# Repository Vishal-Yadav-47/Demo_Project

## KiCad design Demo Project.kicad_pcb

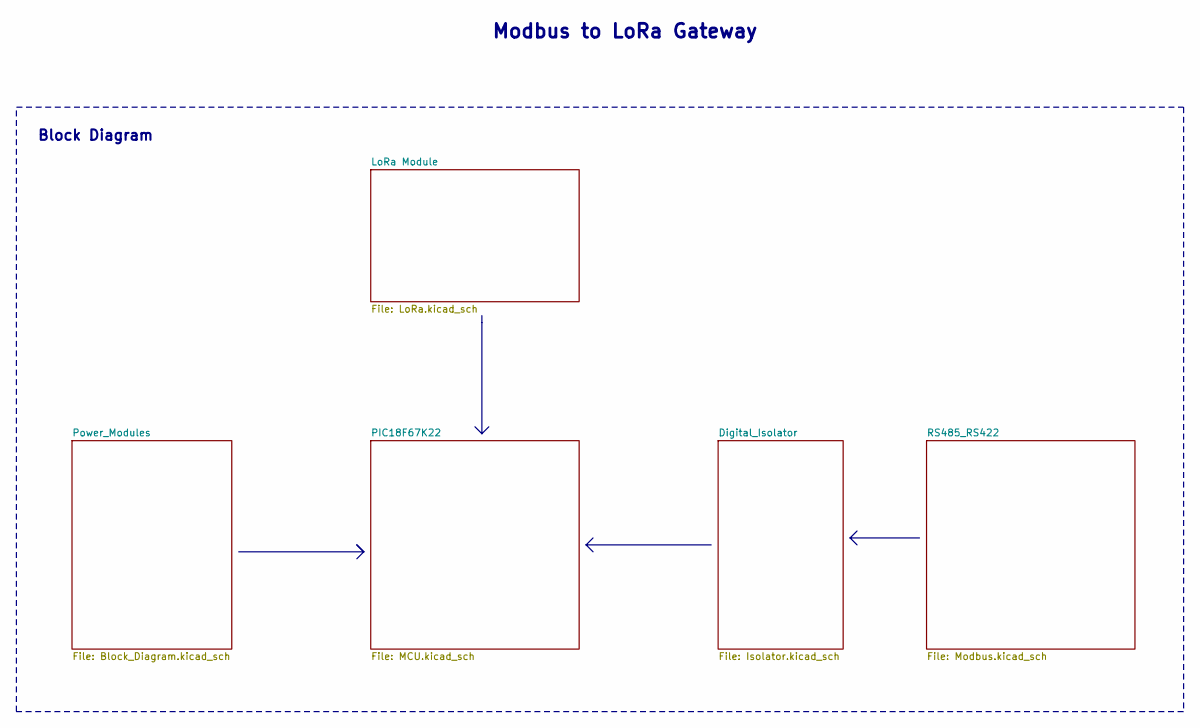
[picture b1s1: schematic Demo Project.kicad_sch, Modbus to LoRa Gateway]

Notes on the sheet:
Modbus to LoRa Gateway
Block Diagram

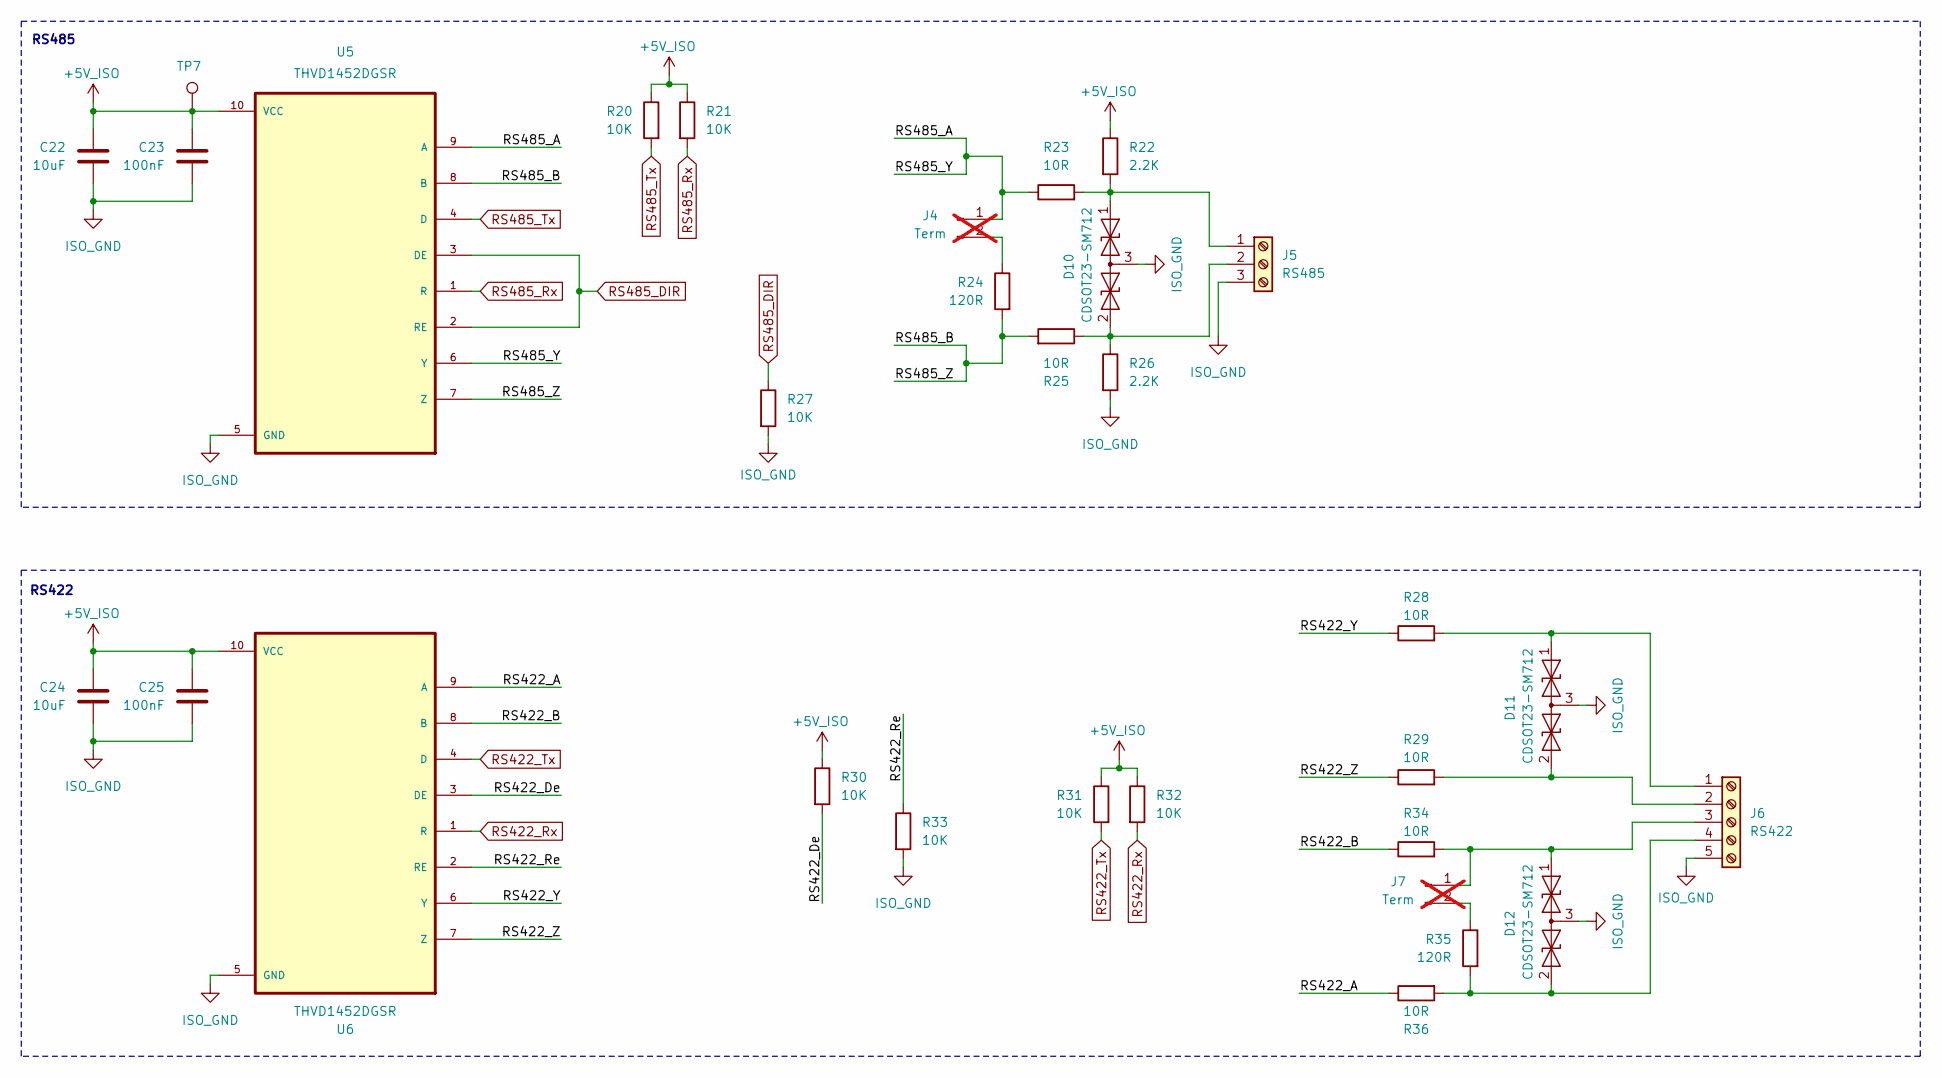
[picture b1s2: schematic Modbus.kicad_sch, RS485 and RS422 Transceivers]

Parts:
C22, C24: 10uF; C_0805_2012Metric
C23, C25: 100nF; C_0805_2012Metric
D10, D11, D12: CDSOT23-SM712; SOT-23
J4, J7: Term; PinHeader_1x02_P2.54mm_Vertical; not fitted
J5: RS485; TerminalBlock_CUI_TB007-508-03_1x03_P5.08mm_Horizontal
J6: RS422; TerminalBlock_CUI_TB007-508-05_1x05_P5.08mm_Horizontal
R20, R21, R27, R30, R31, R32, R33: 10K; R_0805_2012Metric
R22, R26: 2.2K; R_0805_2012Metric
R23, R25, R28, R29, R34, R36: 10R; R_0805_2012Metric
R24, R35: 120R; R_1206_3216Metric
TP7: TestPoint; TestPoint_Pad_D1.0mm
U5, U6: THVD1452DGSR; SOP50P490X110-10N

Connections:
+5V_ISO: C22.1, C23.1, C24.1, C25.1, R20.1, R21.1, R22.1, R30.1, R31.1, R32.1, TP7.1 (1_1), U5.10 (VCC), U6.10 (VCC); also elsewhere on the board
/RS485_RS422/RS422_A: R36.1, U6.9 (A)
/RS485_RS422/RS422_B: R34.1, U6.8 (B)
/RS485_RS422/RS422_De: R30.2, U6.3 (DE)
/RS485_RS422/RS422_Re: R33.1, U6.2 (RE)
/RS485_RS422/RS422_Y: R28.1, U6.6 (Y)
/RS485_RS422/RS422_Z: R29.1, U6.7 (Z)
/RS485_RS422/RS485_A: J4.1, R23.1, U5.6 (Y), U5.9 (A)
/RS485_RS422/RS485_B: R24.2, R25.2, U5.7 (Z), U5.8 (B)
ISO_GND: C22.2, C23.2, C24.2, C25.2, D10.3 (common), D11.3 (common), D12.3 (common), J5.3, J6.5, R26.2, R27.2, R33.2, U5.5 (GND), U6.5 (GND); also elsewhere on the board
unnamed: D10.1 (A1), J5.1, R22.2, R23.2
unnamed: D10.2 (A2), J5.2, R25.1, R26.1
unnamed: D11.1 (A1), J6.1, R28.2
unnamed: D11.2 (A2), J6.2, R29.2
unnamed: D12.1 (A1), J6.3, J7.1, R34.2
unnamed: D12.2 (A2), J6.4, R35.2, R36.2
unnamed: J4.2, R24.1
unnamed: J7.2, R35.1
RS422_Rx: R32.2, U6.1 (R); also elsewhere on the board
RS422_Tx: R31.2, U6.4 (D); also elsewhere on the board
RS485_DIR: R27.1, U5.2 (RE), U5.3 (DE); also elsewhere on the board
RS485_Rx: R21.2, U5.1 (R); also elsewhere on the board
RS485_Tx: R20.2, U5.4 (D); also elsewhere on the board

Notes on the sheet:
RS422
RS485

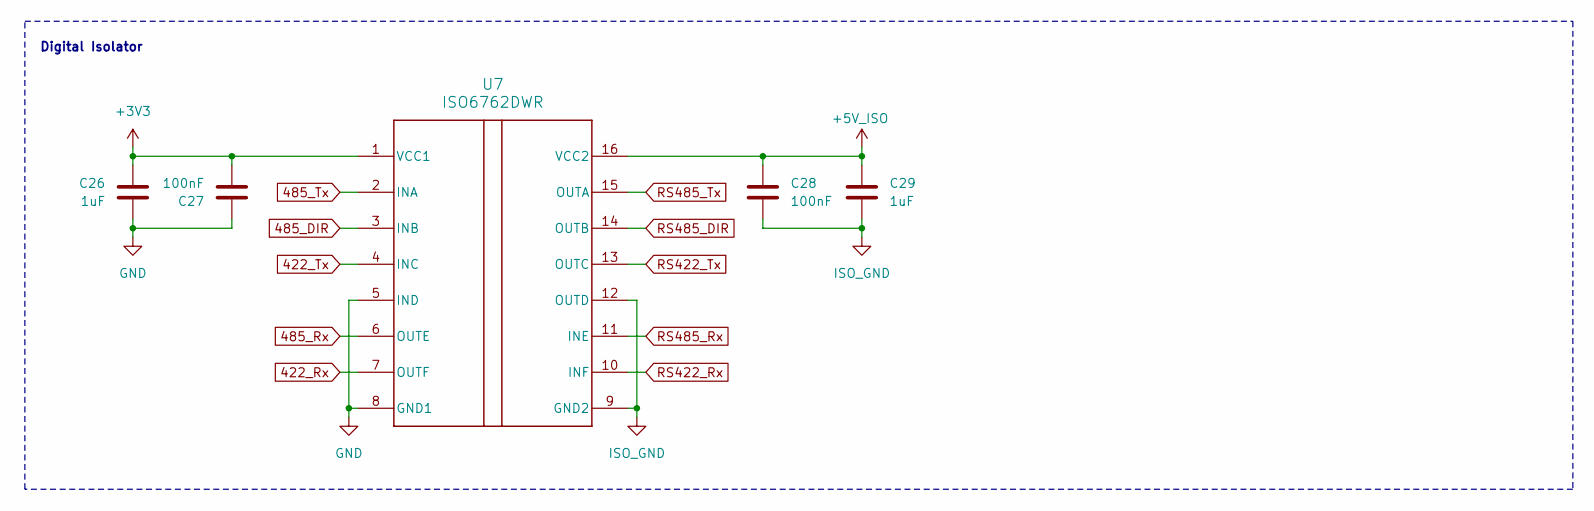
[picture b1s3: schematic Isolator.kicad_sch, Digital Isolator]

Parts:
C26, C29: 1uF; C_0805_2012Metric
C27, C28: 100nF; C_0805_2012Metric
U7: ISO6762DWR; SOIC-16W_7.5x12.8mm_P1.27mm

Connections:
422_Rx: U7.7 (OUTF); also elsewhere on the board
422_Tx: U7.4 (INC); also elsewhere on the board
485_DIR: U7.3 (INB); also elsewhere on the board
485_Rx: U7.6 (OUTE); also elsewhere on the board
485_Tx: U7.2 (INA); also elsewhere on the board
+3V3: C26.2, C27.2, U7.1 (VCC1); also elsewhere on the board
+5V_ISO: C28.1, C29.1, U7.16 (VCC2); also elsewhere on the board
GND: C26.1, C27.1, U7.5 (IND), U7.8 (GND1); also elsewhere on the board
ISO_GND: C28.2, C29.2, U7.9 (GND2), U7.12 (OUTD); also elsewhere on the board
RS422_Rx: U7.10 (INF); also elsewhere on the board
RS422_Tx: U7.13 (OUTC); also elsewhere on the board
RS485_DIR: U7.14 (OUTB); also elsewhere on the board
RS485_Rx: U7.11 (INE); also elsewhere on the board
RS485_Tx: U7.15 (OUTA); also elsewhere on the board

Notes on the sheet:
Digital Isolator

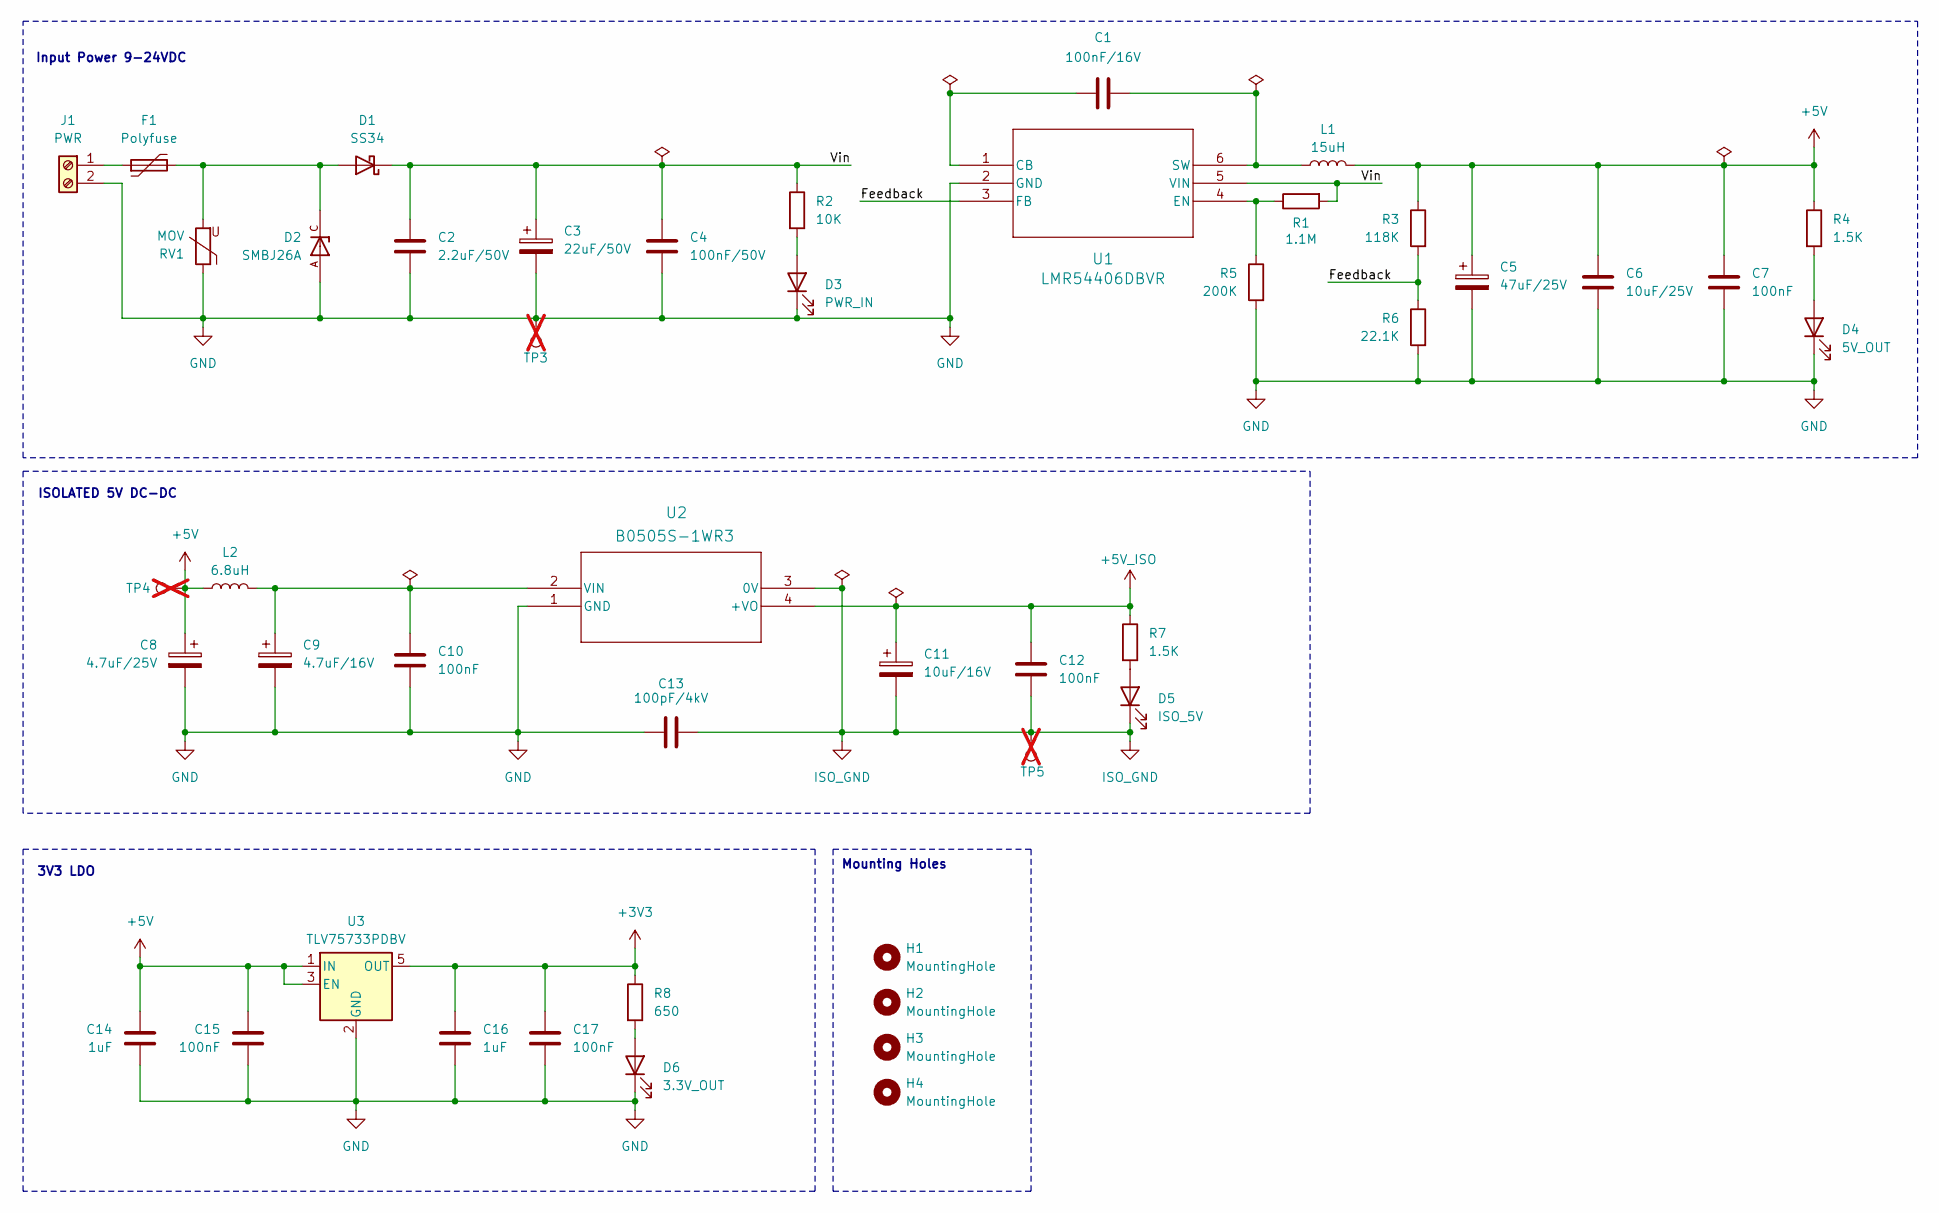
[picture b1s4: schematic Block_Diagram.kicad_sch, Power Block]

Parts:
C1: 100nF/16V; C_0805_2012Metric
C2: 2.2uF/50V; C_0805_2012Metric
C3: 22uF/50V; CP_Elec_8x10.5
C4: 100nF/50V; C_0805_2012Metric
C5: 47uF/25V; CP_Elec_6.3x5.4
C6: 10uF/25V; C_0805_2012Metric
C7, C10, C12, C15, C17: 100nF; C_0805_2012Metric
C8: 4.7uF/25V; CP_Elec_4x5.4
C9: 4.7uF/16V; CP_Elec_4x5.4
C11: 10uF/16V; CP_Elec_5x5.4
C13: 100pF/4kV; C_1812_4532Metric
C14, C16: 1uF; C_0805_2012Metric
D1: SS34; D_SMA
D2: SMBJ26A; DIOM4336X265N; PARTREV F2102
D3: PWR_IN; LED_0805_2012Metric
D4: 5V_OUT; LED_0805_2012Metric
D5: ISO_5V; LED_0805_2012Metric
D6: 3.3V_OUT; LED_0805_2012Metric
F1: Polyfuse; Fuse_2920_7451Metric
H1, H2, H3, H4: MountingHole; MountingHole_3.2mm_M3_DIN965_Pad_TopBottom
J1: PWR; TerminalBlock_CUI_TB007-508-02_1x02_P5.08mm_Horizontal
L1: 15uH; L_Coilcraft_XAL5050-XXX
L2: 6.8uH; L_Wuerth_MAPI-4020
R1: 1.1M; R_0805_2012Metric
R2: 10K; R_0805_2012Metric
R3: 118K; R_0805_2012Metric
R4, R7: 1.5K; R_0805_2012Metric
R5: 200K; R_0805_2012Metric
R6: 22.1K; R_0805_2012Metric
R8: 650; R_0805_2012Metric
RV1: MOV; RV_Disc_D7mm_W3.7mm_P5mm
TP3, TP4, TP5: TestPoint; TestPoint_Pad_D1.0mm; not fitted
U1: LMR54406DBVR; SOT-23-6
U2: B0505S-1WR3; Converter_DCDC_RECOM_R-78S-0.1_THT
U3: TLV75733PDBV; SOT-23-5

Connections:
+3V3: C16.1, C17.1, R8.1, U3.5 (OUT); also elsewhere on the board
+5V: C5.1, C6.1, C7.1, C8.1, C14.1, C15.1, L1.2, L2.1, R3.1, R4.1, TP4.1 (1_1), U3.1 (IN), U3.3 (EN)
+5V_ISO: C11.1, C12.1, R7.1, U2.4 (+VO); also elsewhere on the board
/Power_Modules/Feedback: R3.2, R6.1, U1.3 (FB)
/Power_Modules/Vin: C2.1, C3.1, C4.1, D1.1 (K), R1.2, R2.1, U1.5 (VIN)
GND: C2.2, C3.2, C4.2, C5.2, C6.2, C7.2, C8.2, C9.2, C10.2, C13.1, C14.2, C15.2, C16.2, C17.2, D2.A, D3.1 (K), D4.1 (K), D6.1 (K), J1.2, R5.2, R6.2, RV1.1, TP3.1 (1_1), U1.2 (GND), U2.1 (GND), U3.2 (GND); also elsewhere on the board
ISO_GND: C11.2, C12.2, C13.2, D5.1 (K), TP5.1 (1_1), U2.3 (0V); also elsewhere on the board
unnamed: D1.2 (A), D2.C, F1.2, RV1.2
unnamed: D3.2 (A), R2.2
unnamed: D4.2 (A), R4.2
unnamed: D5.2 (A), R7.2
unnamed: D6.2 (A), R8.2
unnamed: F1.1, J1.1
unnamed: C1.2, U1.1 (CB)
unnamed: R1.1, R5.1, U1.4 (EN)
unnamed: C1.1, L1.1, U1.6 (SW)
unnamed: C9.1, C10.1, L2.2, U2.2 (VIN)

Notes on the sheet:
Mounting Holes
ISOLATED 5V DC-DC
3V3 LDO
Input Power 9-24VDC

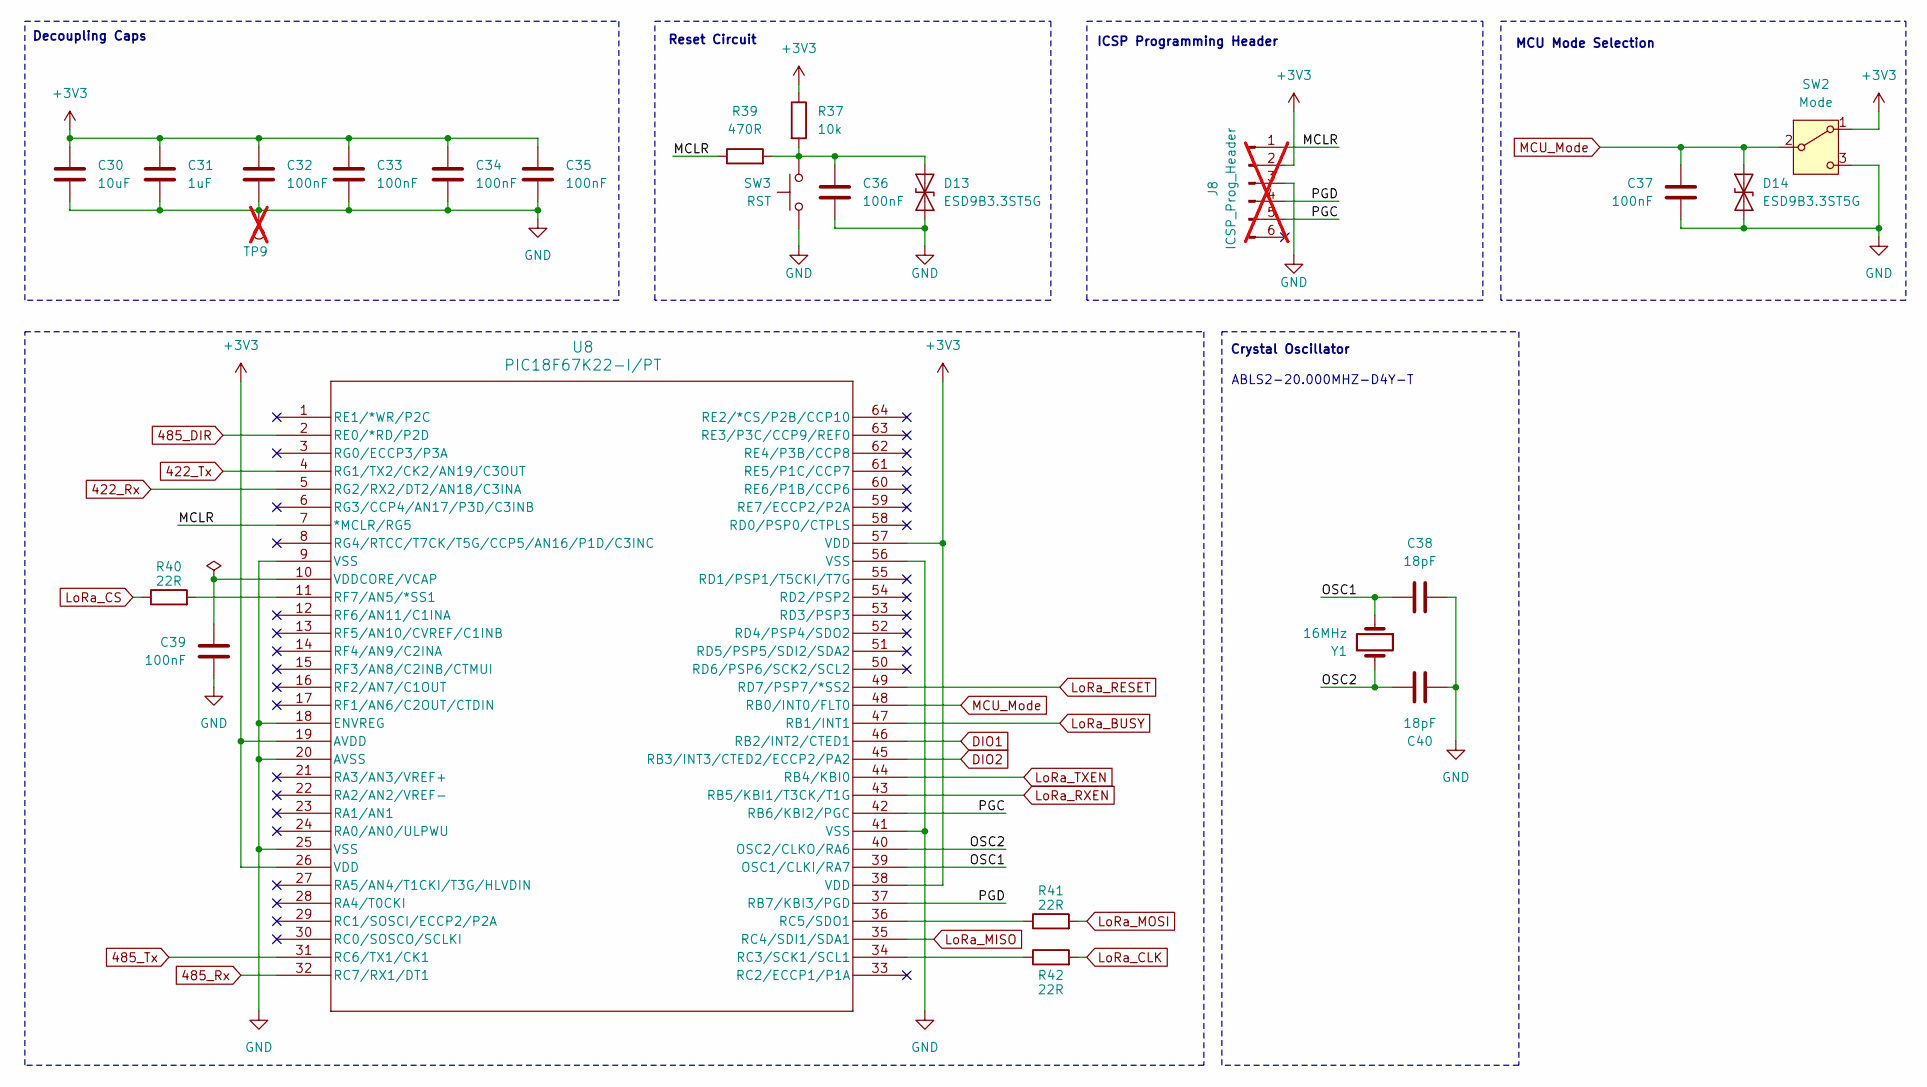
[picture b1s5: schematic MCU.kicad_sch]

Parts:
C30: 10uF; C_0805_2012Metric
C31: 1uF; C_0805_2012Metric
C32, C33, C34, C35, C36, C37, C39: 100nF; C_0805_2012Metric
C38, C40: 18pF; C_0805_2012Metric
D13, D14: ESD9B3.3ST5G; D_SOD-923
J8: ICSP_Prog_Header; PinHeader_1x06_P2.54mm_Vertical; not fitted
R37: 10k; R_0805_2012Metric
R39: 470R; R_0805_2012Metric
R40, R41, R42: 22R; R_0805_2012Metric
SW2: Mode; SW_Slide_SPDT_Straight_CK_OS102011MS2Q
SW3: RST; SW_SPST_TL3305B
TP9: TestPoint; TestPoint_Pad_D1.0mm; not fitted
U8: PIC18F67K22-I/PT; TQFP-64_10x10mm_P0.5mm
Y1: 16MHz; Crystal_SMD_HC49-SD

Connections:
422_Rx: U8.5 (RG2/RX2/DT2/AN18/C3INA); also elsewhere on the board
422_Tx: U8.4 (RG1/TX2/CK2/AN19/C3OUT); also elsewhere on the board
485_DIR: U8.2 (RE0/*RD/P2D); also elsewhere on the board
485_Rx: U8.32 (RC7/RX1/DT1); also elsewhere on the board
485_Tx: U8.31 (RC6/TX1/CK1); also elsewhere on the board
+3V3: C30.1, C31.1, C32.1, C33.1, C34.1, C35.1, J8.2, R37.1, SW2.1 (A), U8.19 (AVDD), U8.26 (VDD), U8.38 (VDD), U8.57 (VDD); also elsewhere on the board
/PIC18F67K22/MCLR: J8.1, R39.1, U8.7 (*MCLR/RG5)
/PIC18F67K22/OSC1: C38.1, U8.39 (OSC1/CLKI/RA7), Y1.1
/PIC18F67K22/OSC2: C40.2, U8.40 (OSC2/CLKO/RA6), Y1.2
/PIC18F67K22/PGC: J8.5, U8.42 (RB6/KBI2/PGC)
/PIC18F67K22/PGD: J8.4, U8.37 (RB7/KBI3/PGD)
DIO1: U8.46 (RB2/INT2/CTED1); also elsewhere on the board
DIO2: U8.45 (RB3/INT3/CTED2/ECCP2/PA2); also elsewhere on the board
GND: C30.2, C31.2, C32.2, C33.2, C34.2, C35.2, C36.2, C37.2, C38.2, C39.2, C40.1, D13.1 (A1), D14.1 (A1), J8.3, SW2.3 (C), SW3.2, TP9.1 (1_1), U8.9 (VSS), U8.18 (ENVREG), U8.20 (AVSS), U8.25 (VSS), U8.41 (VSS), U8.56 (VSS); also elsewhere on the board
LoRa_BUSY: U8.47 (RB1/INT1); also elsewhere on the board
LoRa_CLK: R42.2; also elsewhere on the board
LoRa_CS: R40.1; also elsewhere on the board
LoRa_MISO: U8.35 (RC4/SDI1/SDA1); also elsewhere on the board
LoRa_MOSI: R41.2; also elsewhere on the board
LoRa_RXEN: U8.43 (RB5/KBI1/T3CK/T1G); also elsewhere on the board
LoRa_TXEN: U8.44 (RB4/KBI0); also elsewhere on the board
MCU_Mode: U8.49 (RD7/PSP7/*SS2); also elsewhere on the board
unnamed: C36.1, D13.2 (A2), R37.2, R39.2, SW3.1
unnamed: R42.1, U8.34 (RC3/SCK1/SCL1)
unnamed: R41.1, U8.36 (RC5/SDO1)
unnamed: R40.2, U8.11 (RF7/AN5/*SS1)
unnamed: C39.1, U8.10 (VDDCORE/VCAP)

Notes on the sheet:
ICSP Programming Header
Decoupling Caps
MCU Mode Selection
Crystal Oscillator
ABLS2-20.000MHZ-D4Y-T
Reset Circuit

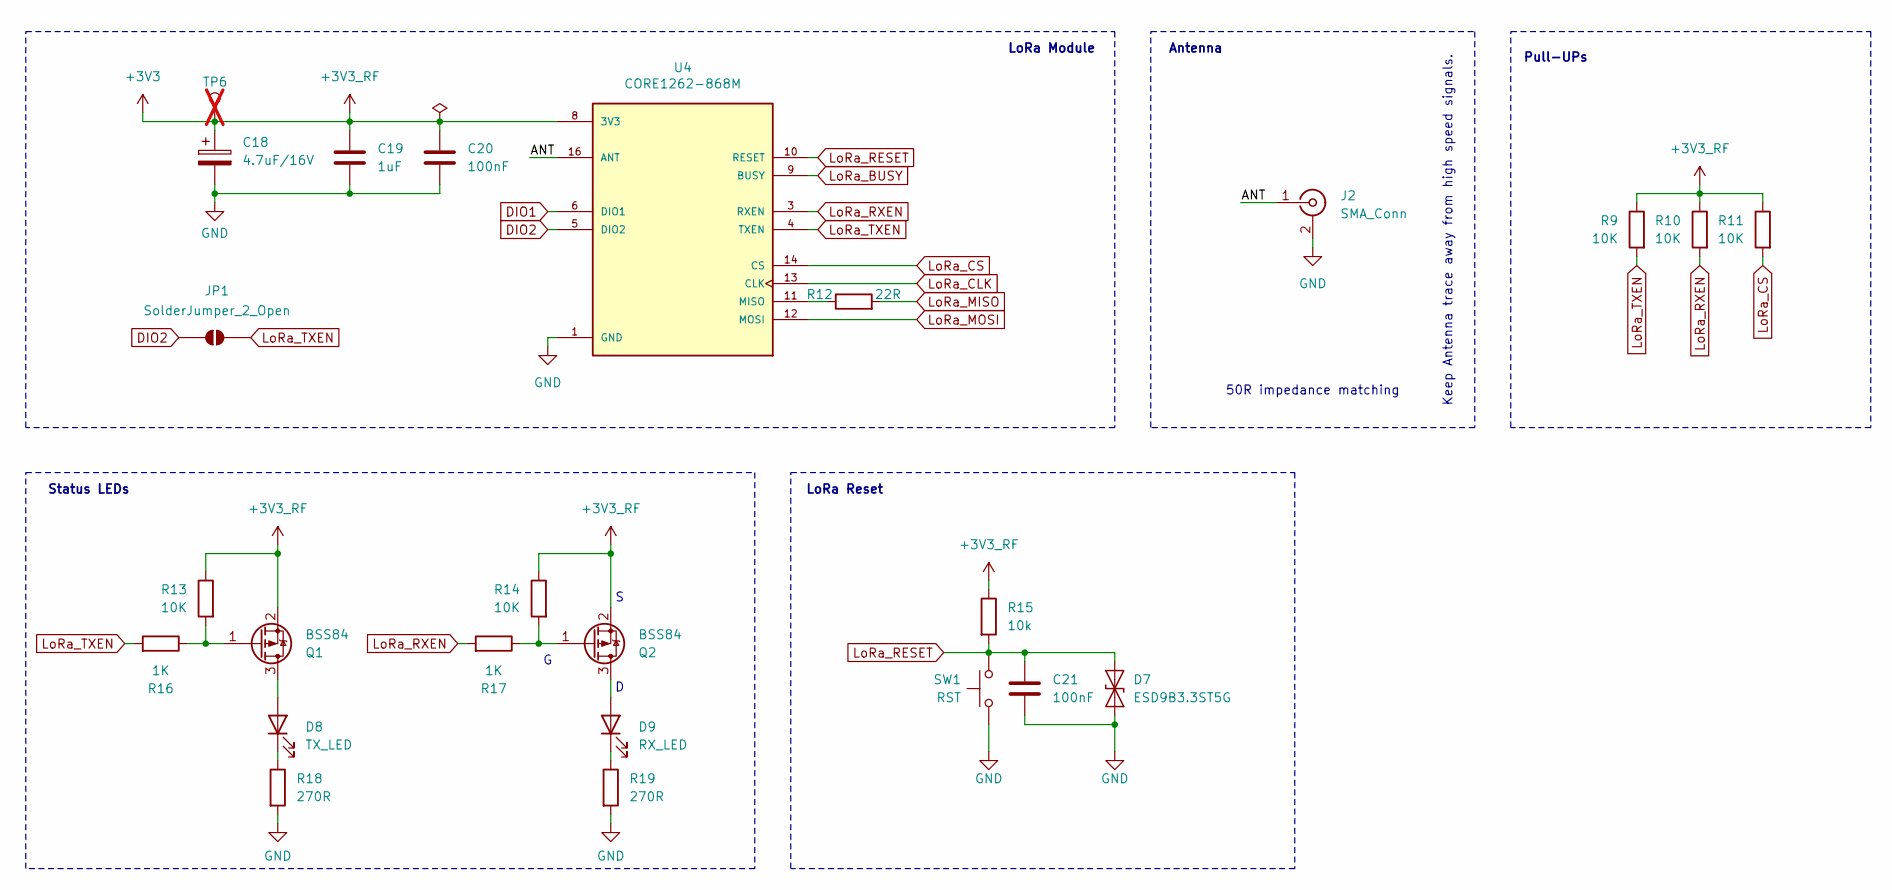
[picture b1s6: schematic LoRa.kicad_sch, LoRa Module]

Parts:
C18: 4.7uF/16V; C_0805_2012Metric
C19: 1uF; C_0805_2012Metric
C20, C21: 100nF; C_0805_2012Metric
D7: ESD9B3.3ST5G; D_SOD-923
D8: TX_LED; LED_0805_2012Metric
D9: RX_LED; LED_0805_2012Metric
J2: SMA_Conn; SMA_Amphenol_901-143_Horizontal
JP1: SolderJumper_2_Open; SolderJumper-2_P1.3mm_Open_TrianglePad1.0x1.5mm
Q1, Q2: BSS84; SOT-23
R9, R10, R11, R13, R14: 10K; R_0805_2012Metric
R12: 22R; R_0805_2012Metric
R15: 10k; R_0805_2012Metric
R16, R17: 1K; R_0805_2012Metric
R18, R19: 270R; R_0805_2012Metric
SW1: RST; SW_SPST_TL3305B
TP6: TestPoint; TestPoint_Pad_D1.0mm; not fitted
U4: CORE1262-868M; XCVR_CORE1262-868M; PARTREV N/A

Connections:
+3V3: C18.1, C19.1, C20.1, Q1.2 (S), Q2.2 (S), R9.1, R10.1, R11.1, R13.1, R14.1, R15.1, TP6.1 (1_1), U4.8 (3V3); also elsewhere on the board
/LoRa Module/ANT: J2.1 (In), U4.16 (ANT)
DIO1: U4.6 (DIO1); also elsewhere on the board
DIO2: JP1.2 (B), U4.5 (DIO2); also elsewhere on the board
GND: C18.2, C19.2, C20.2, C21.2, D7.1 (A1), J2.2 (Ext), R18.2, R19.2, SW1.2, U4.1 (GND), U4.2 (GND), U4.7 (GND), U4.15 (GND); also elsewhere on the board
LoRa_BUSY: U4.9 (BUSY); also elsewhere on the board
LoRa_CLK: U4.13 (CLK); also elsewhere on the board
LoRa_CS: R11.2, U4.14 (CS); also elsewhere on the board
LoRa_MISO: R12.2; also elsewhere on the board
LoRa_MOSI: U4.12 (MOSI); also elsewhere on the board
LoRa_RXEN: R10.2, R17.2, U4.3 (RXEN); also elsewhere on the board
LoRa_TXEN: JP1.1 (A), R9.2, R16.2, U4.4 (TXEN); also elsewhere on the board
unnamed: D8.2 (A), Q1.3 (D)
unnamed: D8.1 (K), R18.1
unnamed: D9.2 (A), Q2.3 (D)
unnamed: D9.1 (K), R19.1
unnamed: Q1.1 (G), R13.2, R16.1
unnamed: Q2.1 (G), R14.2, R17.1
unnamed: R12.1, U4.11 (MISO)

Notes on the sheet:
LoRa Module
LoRa Reset
Status LEDs
Antenna
Keep Antenna trace away from high speed signals.
50R impedance matching
Pull-UPs

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
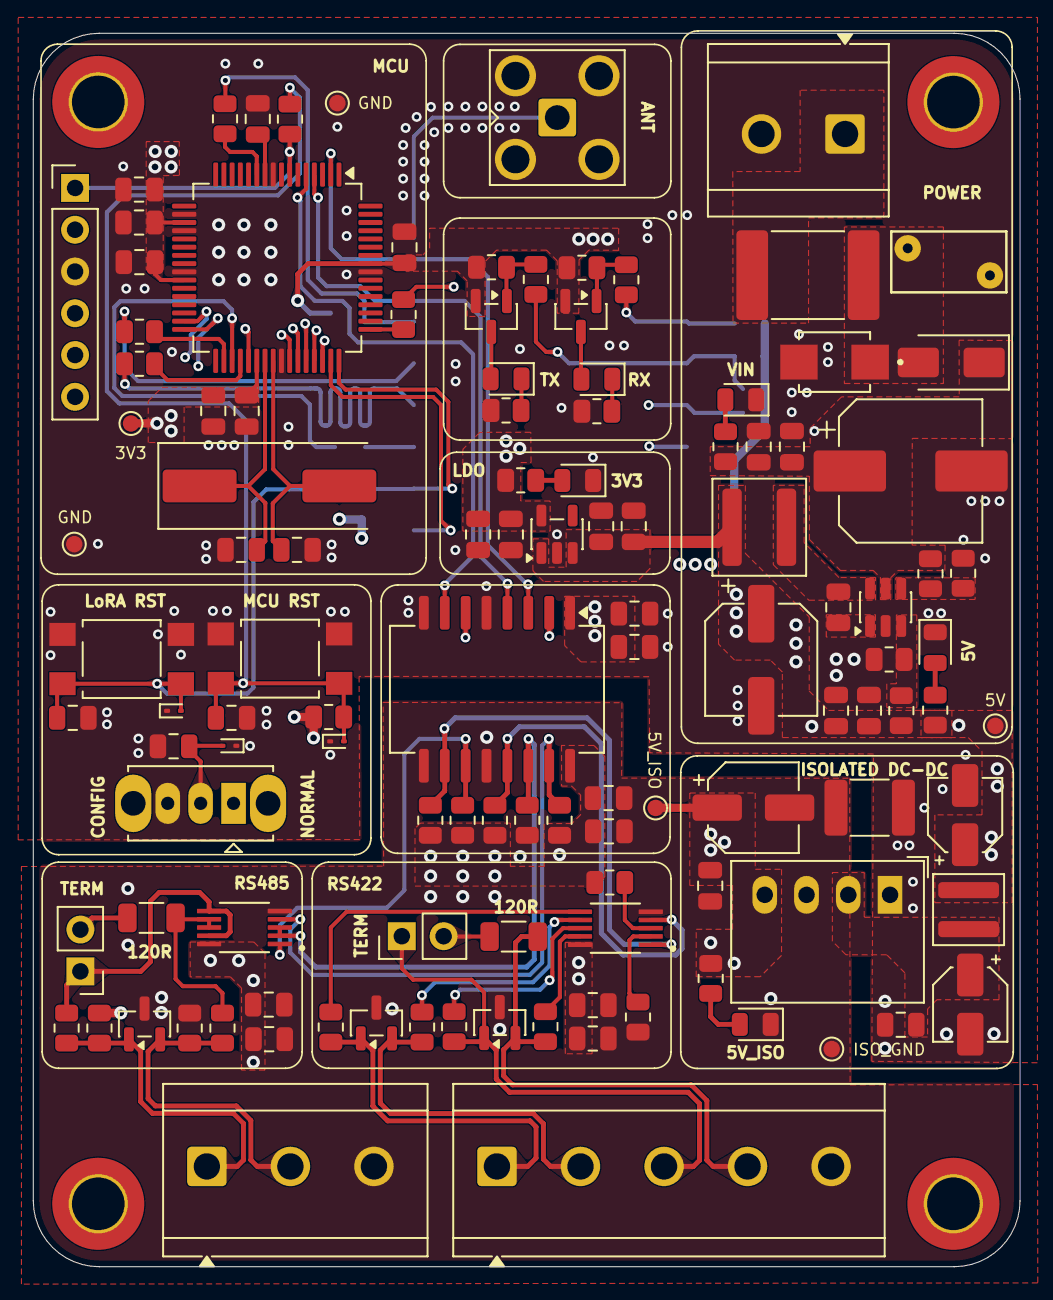
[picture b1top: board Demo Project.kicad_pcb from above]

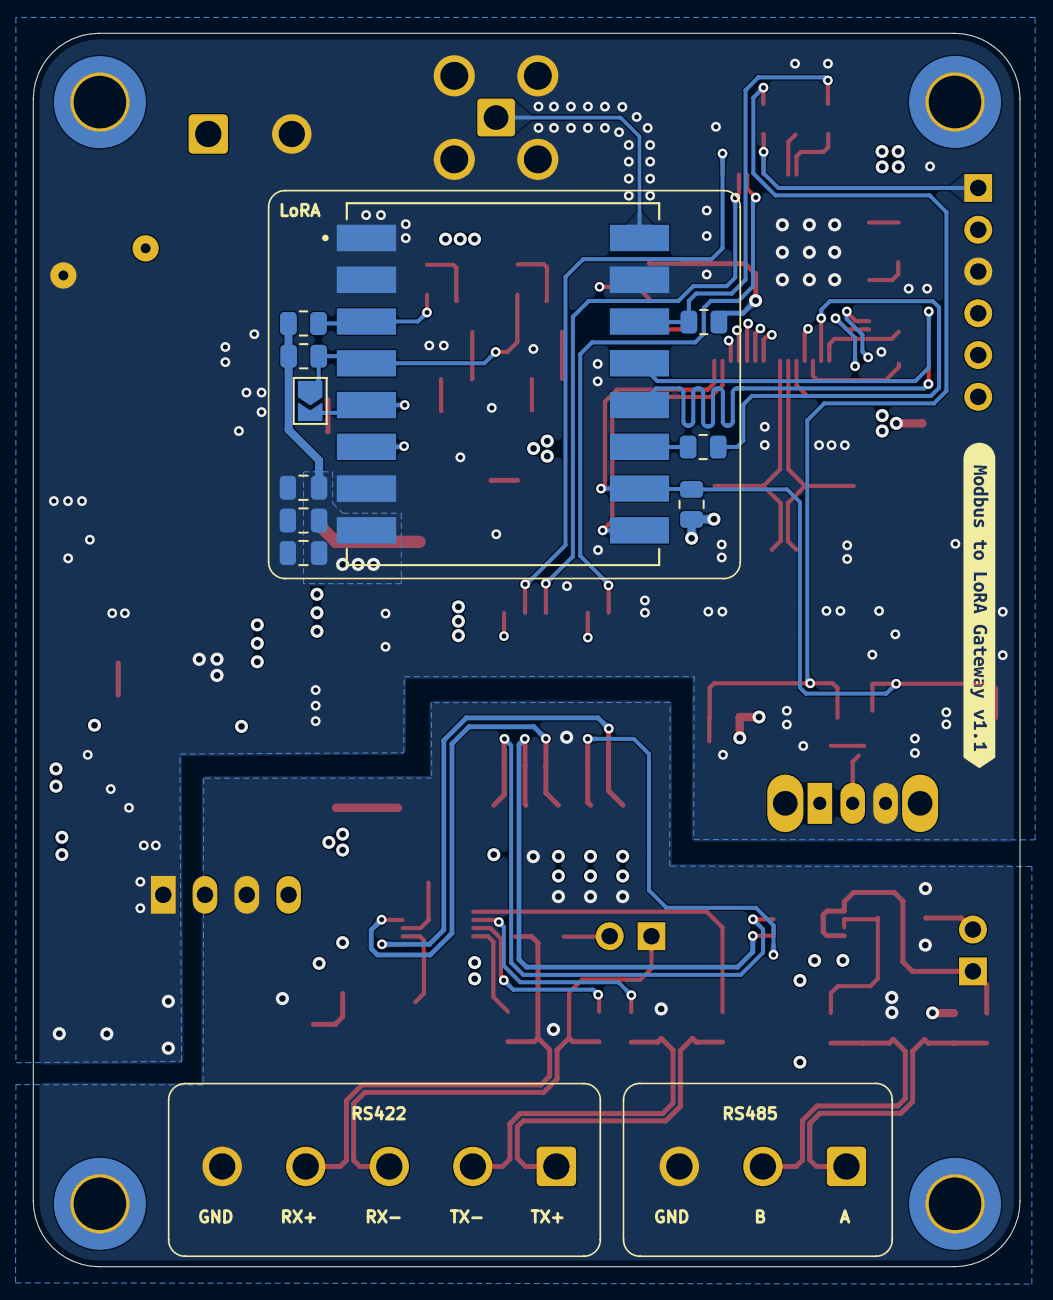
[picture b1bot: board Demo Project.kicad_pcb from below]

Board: 4 copper layers, 60.0 x 75.0 mm, 129 parts (11 on the bottom side), 73 nets.

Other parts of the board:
R38: 330R; R_0805_2012Metric
kibuzzard-6A9A594E: G***; kibuzzard-6A9A594E

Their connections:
MCU_Mode: R38.1; also elsewhere on the board

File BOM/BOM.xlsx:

Reference | Qty | Value | Footprint | MPN
C1 | 1 | 100nF/16V | Capacitor_SMD:C_0805_2012Metric | GRM21BR71C105KA01L
C2 | 1 | 2.2uF/50V | Capacitor_SMD:C_0805_2012Metric | GCM21BM8EH225KE08L
C3 | 1 | 22uF/50V | Capacitor_SMD:CP_Elec_8x10.5 | EDT226M050S9LAA
C4 | 1 | 100nF/50V | Capacitor_SMD:C_0805_2012Metric | GCD21BR71H104KA01L
C5 | 1 | 47uF/25V | Capacitor_SMD:CP_Elec_6.3x5.4 | EDK476M025A9GAA
C6 | 1 | 10uF/25V | Capacitor_SMD:C_0805_2012Metric | GRM21BR61E106MA73L
C7,C10,C12,C15,C17,C20,C21,C23,C25,C27,C28,C32,C33,C34,C35,C36,C37,C39 | 18 | 100nF | Capacitor_SMD:C_0805_2012Metric | GCD21BR71H104KA01L
C8 | 1 | 4.7uF/25V | Capacitor_SMD:CP_Elec_4x5.4 | EDK475M025A9BAA
C9,C18 | 2 | 4.7uF/16V | Capacitor_SMD:CP_Elec_4x5.4 | UWP1C4R7MCL1GB
C11 | 1 | 10uF/16V | Capacitor_SMD:CP_Elec_5x5.4 | EEE-1CA100NR
C13 | 1 | 100pF/2kV | Capacitor_SMD:C_1812_4532Metric | C1812C103KGRACTU
C14,C16,C19,C26,C29,C31 | 6 | 1uF | Capacitor_SMD:C_0805_2012Metric | GCM21BR71H105KA03L
C22,C24,C30 | 3 | 10uF | Capacitor_SMD:C_0805_2012Metric | GRM21BR61E106MA73L
C38,C40 | 2 | 18pF | Capacitor_SMD:C_0805_2012Metric | CC0805FRNPO9BN180
D1 | 1 | SS34 | Diode_SMD:D_SMA | SS34
D2 | 1 | SMBJ26A | SMBJ26A:DIOM4336X265N | SMBJ26A
D3 | 1 | PWR_IN | LED_SMD:LED_0805_2012Metric | LTST-C170KRKT
D4 | 1 | 5V_OUT | LED_SMD:LED_0805_2012Metric | LTST-C170KRKT
D5 | 1 | ISO_5V | LED_SMD:LED_0805_2012Metric | LTST-C170KRKT
D6 | 1 | 3.3V_OUT | LED_SMD:LED_0805_2012Metric | LTST-C170KRKT
D7,D13,D14 | 3 | ESD9B3.3ST5G | Diode_SMD:D_SOD-923 | ESD9B3.3ST5G
D8 | 1 | TX_LED | LED_SMD:LED_0805_2012Metric | LTST-C170KRKT
D9 | 1 | RX_LED | LED_SMD:LED_0805_2012Metric | LTST-C170GKT
D10,D11,D12 | 3 | CDSOT23-SM712 | Package_TO_SOT_SMD:SOT-23 | CDSOT23-SM712
F1 | 1 | Polyfuse | Fuse:Fuse_2920_7451Metric | 2920L075/60MR
J1 | 1 | PWR | TerminalBlock_CUI:TerminalBlock_CUI_TB007-508-02_1x02_P5.08mm_Horizontal | TB007-508-02BE
J2 | 1 | SMA_Conn | Connector_Coaxial:SMA_Amphenol_901-143_Horizontal | SMA-J-P-H-RA-TH1
J5 | 1 | RS485 | TerminalBlock_CUI:TerminalBlock_CUI_TB007-508-03_1x03_P5.08mm_Horizontal | TB007-508-03BE
J6 | 1 | RS422 | TerminalBlock_CUI:TerminalBlock_CUI_TB007-508-05_1x05_P5.08mm_Horizontal | TB007-508-05BE
L1 | 1 | 15uH | Inductor_SMD:L_Coilcraft_XAL5050-XXX | 744393305150
L2 | 1 | 6.8uH | Inductor_SMD:L_Wuerth_MAPI-4020 | 74438335068
Q1,Q2 | 2 | BSS84 | Package_TO_SOT_SMD:SOT-23 | BSS84
R1 | 1 | 1.1M | Resistor_SMD:R_0805_2012Metric | RC0805FR-071M1L
R2,R9,R10,R11,R13,R14,R20,R21,R27,R30,R31,R32,R33 | 13 | 10K | Resistor_SMD:R_0805_2012Metric | RC0805FR-0710KL
R3 | 1 | 118K | Resistor_SMD:R_0805_2012Metric | RC0805FR-07118KL
R4,R7 | 2 | 1.5K | Resistor_SMD:R_0805_2012Metric | RC0805FR-071K5L
R5 | 1 | 200K | Resistor_SMD:R_0805_2012Metric | RC0805FR-07200KL
R6 | 1 | 22.1K | Resistor_SMD:R_0805_2012Metric | RC0805FR-0722K1L
R8 | 1 | 650 | Resistor_SMD:R_0805_2012Metric | RC0805FR-07650RL
R12,R40,R41,R42 | 4 | 22R | Resistor_SMD:R_0805_2012Metric | RC0805FR-0722RL
R15,R37 | 2 | 10k | Resistor_SMD:R_0805_2012Metric | RC0805FR-0710KL
R16,R17 | 2 | 1K | Resistor_SMD:R_0805_2012Metric | RC0805FR-071KL
R18,R19 | 2 | 270R | Resistor_SMD:R_0805_2012Metric | RC0805FR-07270RL
R22,R26 | 2 | 2.2K | Resistor_SMD:R_0805_2012Metric | RC0805FR-072K2L
R23,R25,R28,R29,R34,R36 | 6 | 10R | Resistor_SMD:R_0805_2012Metric | RC0805FR-0710RL
R24,R35 | 2 | 120R | Resistor_SMD:R_1206_3216Metric | AC1206FR-07120RL
R38 | 1 | 330R | Resistor_SMD:R_0805_2012Metric | RC0805FR-07330RL
R39 | 1 | 470R | Resistor_SMD:R_0805_2012Metric | RC0805FR-07470RL
RV1 | 1 | MOV | Varistor:RV_Disc_D7mm_W3.7mm_P5mm | V39ZA1
SW1,SW3 | 2 | RST | Button_Switch_SMD:SW_SPST_TL3305B | TL3305BF260QG
SW2 | 1 | Mode | Button_Switch_THT:SW_Slide_SPDT_Straight_CK_OS102011MS2Q | OS102011MS2Q
U1 | 1 | LMR54406DBVR | Package_TO_SOT_SMD:SOT-23-6 | LMR54406DBVR
U2 | 1 | B0505S-1WR3 | Converter_DCDC:Converter_DCDC_RECOM_R-78S-0.1_THT | B0505S-1WR3
U3 | 1 | TLV75733PDBV | Package_TO_SOT_SMD:SOT-23-5 | TLV75733PDBV
U4 | 1 | CORE1262-868M | CORE1262-868M:XCVR_CORE1262-868M | Core1262 HF
U5,U6 | 2 | THVD1452DGSR | THVD1452DGSR:SOP50P490X110-10N | THVD1452DGSR
U7 | 1 | ISO6762DWR | Package_SO:SOIC-16W_7.5x12.8mm_P1.27mm | ISO6762DWR
U8 | 1 | PIC18F67K22-I/PT | Package_QFP:TQFP-64_10x10mm_P0.5mm | PIC18F67K22-I/PT
Y1 | 1 | 20MHz | Crystal:Crystal_SMD_HC49-SD | ABLS2-20.000MHZ-D4Y-T
